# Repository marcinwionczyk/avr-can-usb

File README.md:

##avr-can-usb firmware

This code is under development and is not mature.

I'm using chips like: atmega644pa, MCP2515, TJA1042T.
Communication with PC is done over UART-USB converter FT230XS and is galvanically separated from the rest chips with 
VO0611 optocouplers.

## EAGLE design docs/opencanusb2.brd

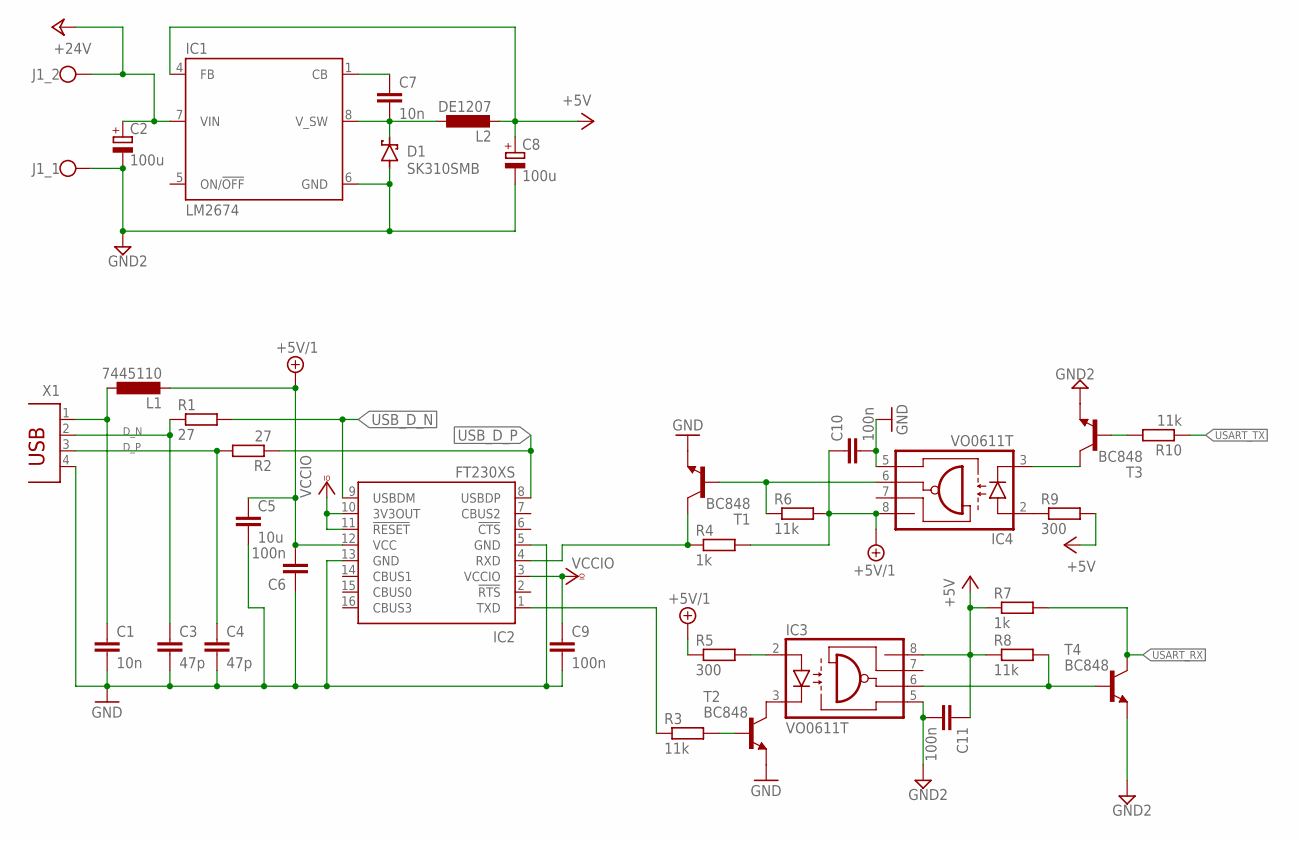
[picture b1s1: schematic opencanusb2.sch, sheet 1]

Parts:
C1: 10n; C0402
C2, C8: 100u; E5-8,5
C3, C4: 47p; C0603
C5: 10u; C1210K
C6, C9, C10, C11: 100n; C0805
C7: 10n; C0805
D1: SK310SMB; SMB
IC1: LM2674; SOIC127P599X265-8N
IC2: FT230XS; SSOP16
IC3, IC4: VO0611T; SOIC127P610X323-8N
J1: DG300-7.5
L1: 7445110
L2: DE1207; INDC120120X800N
R1, R2: 27; R0805
R3, R6, R8, R10: 11k; R1206
R4, R7: 1k; R0805
R5, R9: 300; R0805
T1, T2, T3, T4: BC848; SOT23
X1: PN61729

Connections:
+5V: C8.+, C11.1, IC1.4 (FB), IC3.8 (VCC), L2.2, R7.1, R8.1, R9.2; also elsewhere on the board
+5V/1: C5.1, C6.2, C10.1, IC2.12 (VCC), IC4.8 (VCC), L1.2, R4.2, R5.1, R6.2
+24V: C2.+, IC1.7 (VIN), J1.P$2; also elsewhere on the board
D_N: C3.1, R1.1, X1.2
D_P: C4.1, R2.2, X1.3
GND: C1.2, C3.2, C4.2, C5.2, C6.1, C9.2, C10.2, IC2.5 (GND), IC2.13 (GND), IC4.5 (GND), T1.2 (E), T2.2 (E), X1.4
GND2: C2.-, C8.-, C11.2, D1.A, IC1.6 (GND), IC3.5 (GND), J1.P$1, T3.2 (E), T4.2 (E); also elsewhere on the board
unnamed: IC3.2 (A), R5.2
unnamed: IC2.1 (TXD), R3.1
unnamed: IC3.3 (C), T2.3 (C)
unnamed: IC4.2 (A), R9.1
unnamed: IC4.3 (C), T3.3 (C)
unnamed: IC4.6 (VO), R6.1, T1.1 (B)
unnamed: R3.2, T2.1 (B)
unnamed: IC3.6 (VO), R8.2, T4.1 (B)
unnamed: R10.2, T3.1 (B)
unnamed: IC2.4 (RXD), R4.1, T1.3 (C)
unnamed: C1.1, L1.1, X1.1
unnamed: C7.2, D1.C, IC1.8 (V_SW), L2.1
unnamed: C7.1, IC1.1 (CB)
ON/!OFF: IC1.5 (ON/!OFF)
USART_RX: R7.2, T4.3 (C); also elsewhere on the board
USART_TX: R10.1; also elsewhere on the board
USB_D_N: IC2.9 (USBDM), R1.2
USB_D_P: IC2.8 (USBDP), R2.1
VCCIO: C9.1, IC2.3 (VCCIO), IC2.10 (3V3OUT), IC2.11 (!RESET)

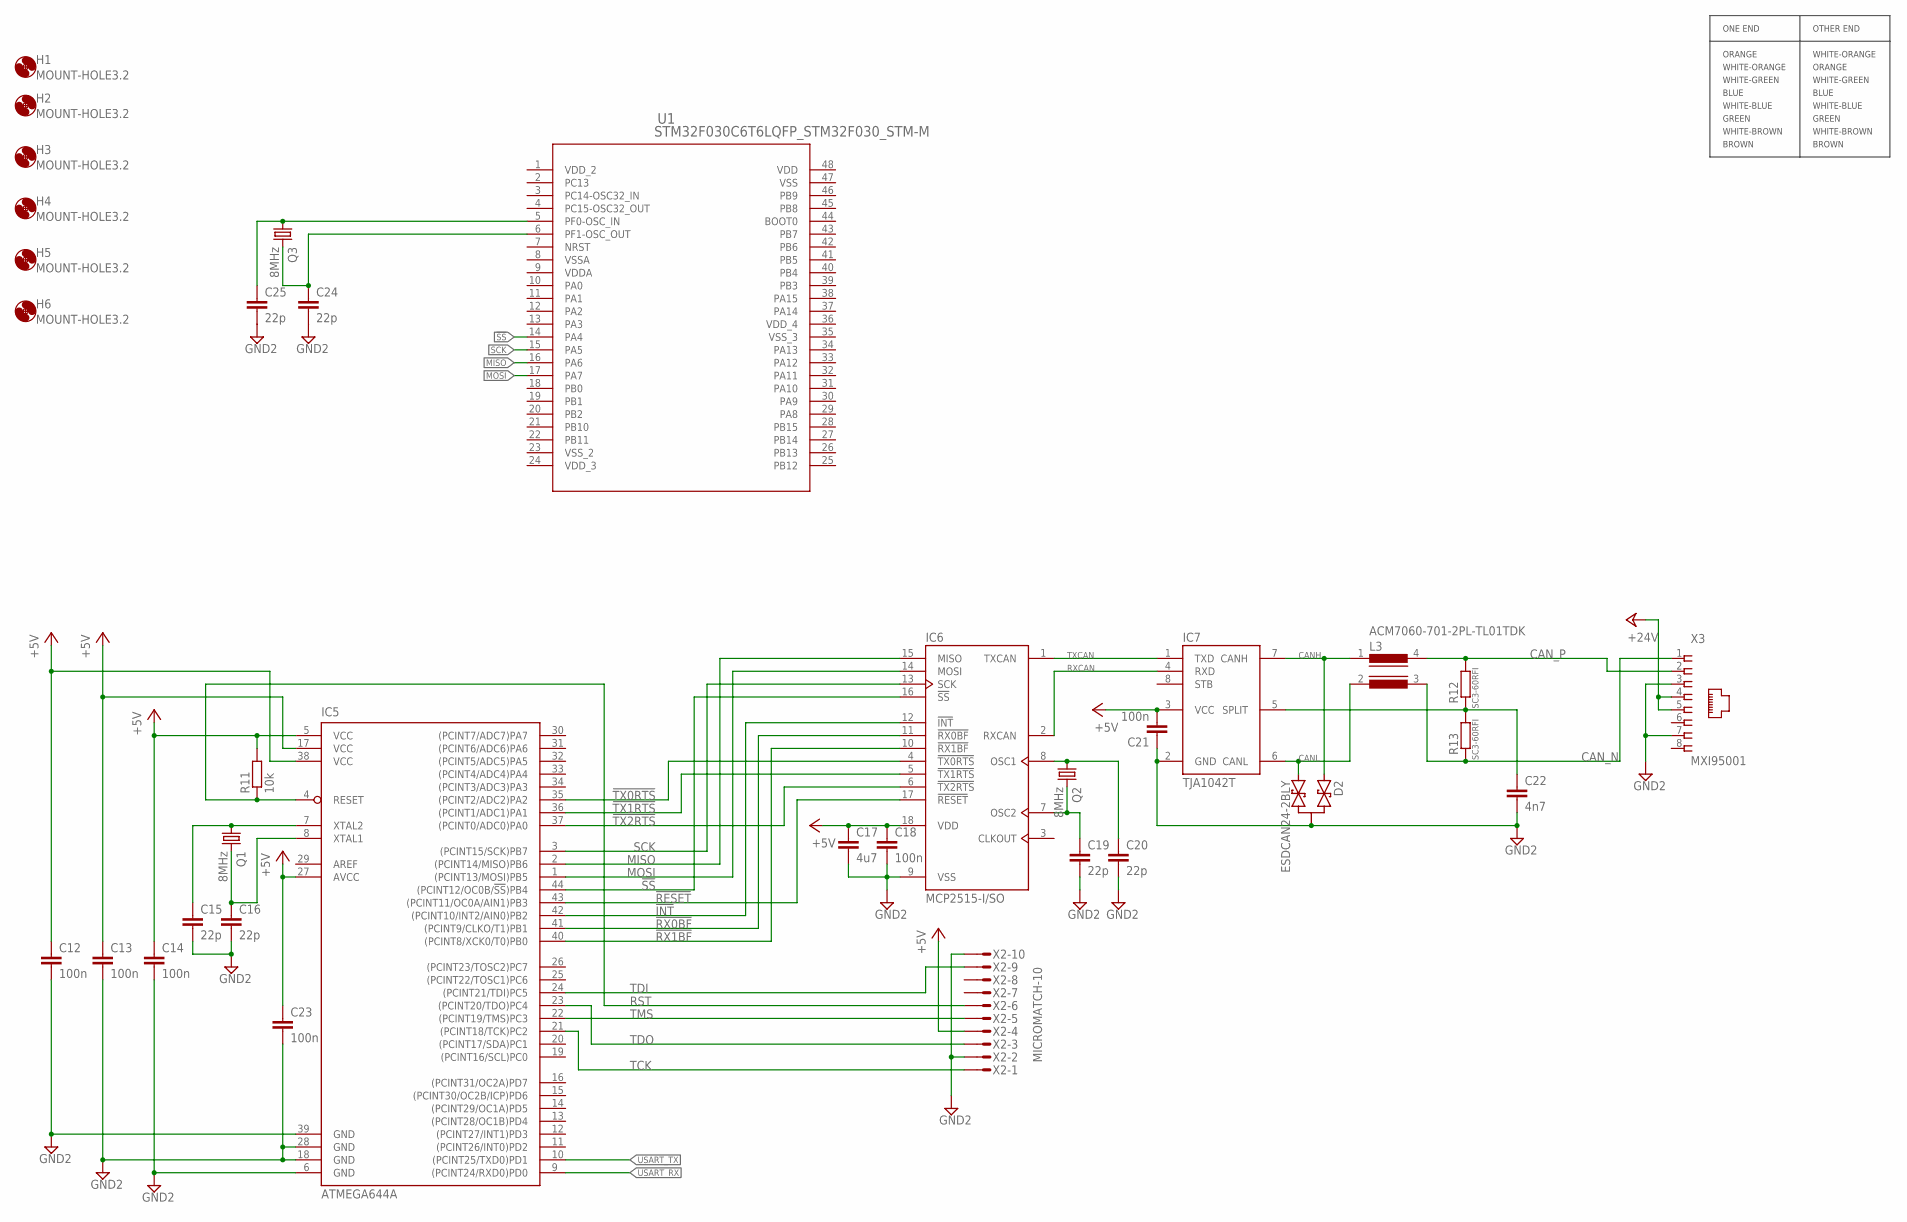
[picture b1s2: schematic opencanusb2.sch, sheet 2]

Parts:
C12, C13, C14, C18, C21, C23: 100n; C0805
C15, C16, C19, C20, C24, C25: 22p; C0805
C17: 4u7; C0805
C22: 4n7; C0805
D2: ESDCAN24-2BLY; SOT95P255X140-3N
H1, H2, H3, H4, H5, H6: MOUNT-HOLE3.2; 3,2
IC5: ATMEGA644A; TQFP44
IC6: MCP2515-I/SO; SOIC127P1030X265-18N
IC7: TJA1042T; SOIC127P600X265-8N
L3: ACM7060-701-2PL-TL01TDK
Q1, Q2, Q3: 8MHz; HC49UP
R11: 10k; R1206
R12, R13: SC3-60RFI; RESC3163X76N
U1: STM32F030C6T6LQFP_STM32F030_STM-M; LQFP_STM32F030_STM-M
X2: MICROMATCH-10
X3: MXI95001; MXI950001

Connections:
!INT: IC5.42 ((PCINT10/INT2/AIN0)PB2), IC6.12 (!INT)
!RESET: IC5.43 ((PCINT11/OC0A/AIN1)PB3), IC6.17 (!RESET)
!RX0BF: IC5.41 ((PCINT9/CLKO/T1)PB1), IC6.11 (!RX0BF)
!RX1BF: IC5.40 ((PCINT8/XCK0/T0)PB0), IC6.10 (!RX1BF)
!SS: IC5.44 ((PCINT12/OC0B/!SS!)PB4), IC6.16 (!SS), U1.14 (PA4)
!TX0RTS: IC5.35 ((PCINT2/ADC2)PA2), IC6.4 (!TX0RTS)
!TX1RTS: IC5.36 ((PCINT1/ADC1)PA1), IC6.5 (!TX1RTS)
!TX2RTS: IC5.37 ((PCINT0/ADC0)PA0), IC6.6 (!TX2RTS)
+5V: C12.1, C13.1, C14.1, C17.1, C18.1, C21.2, C23.1, IC5.5 (VCC), IC5.17 (VCC), IC5.27 (AVCC), IC5.38 (VCC), IC6.18 (VDD), IC7.3 (VCC), R11.2, X2.4; also elsewhere on the board
+24V: X3.4, X3.5; also elsewhere on the board
CANH: D2.1, IC7.7 (CANH), L3.1
CANL: D2.2, IC7.6 (CANL), L3.2
CAN_N: L3.3, R13.1, X3.1
CAN_P: L3.4, R12.2, X3.2
GND2: C12.2, C13.2, C14.2, C15.2, C16.2, C17.2, C18.2, C19.2, C20.2, C21.1, C22.2, C23.2, C24.2, C25.2, D2.3, IC5.6 (GND), IC5.18 (GND), IC5.28 (GND), IC5.39 (GND), IC6.9 (VSS), IC7.2 (GND), X2.2, X2.10, X3.3, X3.7; also elsewhere on the board
MISO: IC5.2 ((PCINT14/MISO)PB6), IC6.15 (MISO), U1.16 (PA6)
MOSI: IC5.1 ((PCINT13/MOSI)PB5), IC6.14 (MOSI), U1.17 (PA7)
unnamed: C25.1, Q3.1, U1.5 (PF0-OSC_IN)
unnamed: C24.1, Q3.2, U1.6 (PF1-OSC_OUT)
unnamed: C15.1, IC5.7 (XTAL2), Q1.1
unnamed: C19.1, IC6.7 (OSC2), Q2.2
unnamed: C16.1, IC5.8 (XTAL1), Q1.2
unnamed: C20.1, IC6.8 (OSC1), Q2.1
unnamed: C22.1, IC7.5 (SPLIT), R12.1, R13.2
RST: IC5.4 (RESET), R11.1, X2.6
RXCAN: IC6.2 (RXCAN), IC7.4 (RXD)
SCK: IC5.3 ((PCINT15/SCK)PB7), IC6.13 (SCK), U1.15 (PA5)
TCK: IC5.21 ((PCINT18/TCK)PC2), X2.1
TDI: IC5.24 ((PCINT21/TDI)PC5), X2.9
TDO: IC5.23 ((PCINT20/TDO)PC4), X2.3
TMS: IC5.22 ((PCINT19/TMS)PC3), X2.5
TXCAN: IC6.1 (TXCAN), IC7.1 (TXD)
USART_RX: IC5.9 ((PCINT24/RXD0)PD0); also elsewhere on the board
USART_TX: IC5.10 ((PCINT25/TXD0)PD1); also elsewhere on the board
VDD: U1.48 (VDD)
VDDA: U1.9 (VDDA)
VDD_2: U1.1 (VDD_2)
VDD_3: U1.24 (VDD_3)
VDD_4: U1.36 (VDD_4)

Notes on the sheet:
ORANGE
WHITE-ORANGE
WHITE-GREEN
BLUE
WHITE-BLUE
GREEN
WHITE-BROWN
ONE END
OTHER END
BROWN

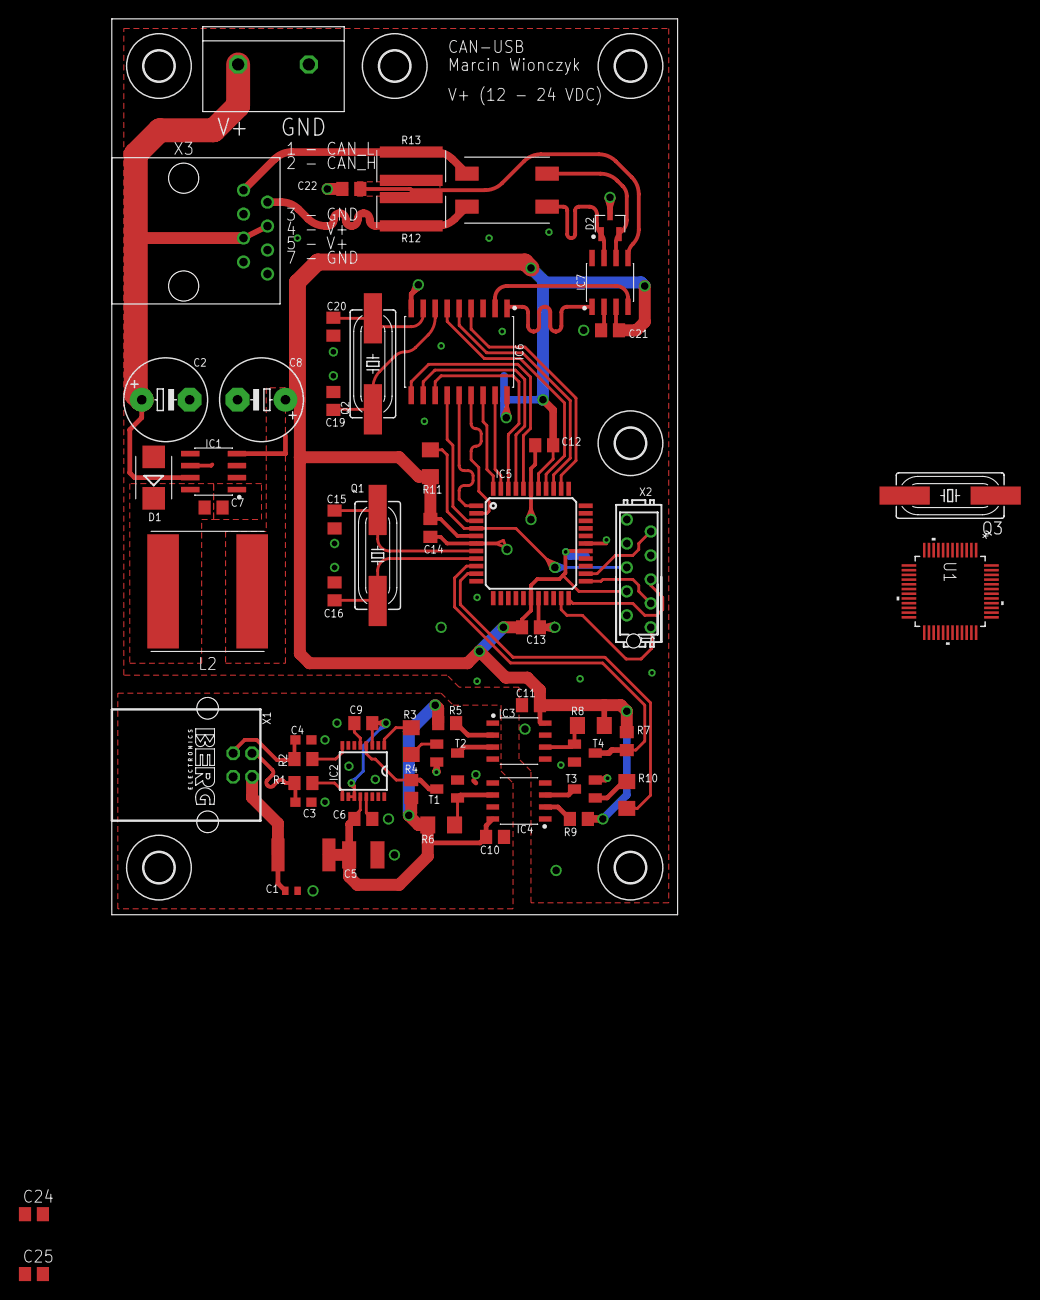
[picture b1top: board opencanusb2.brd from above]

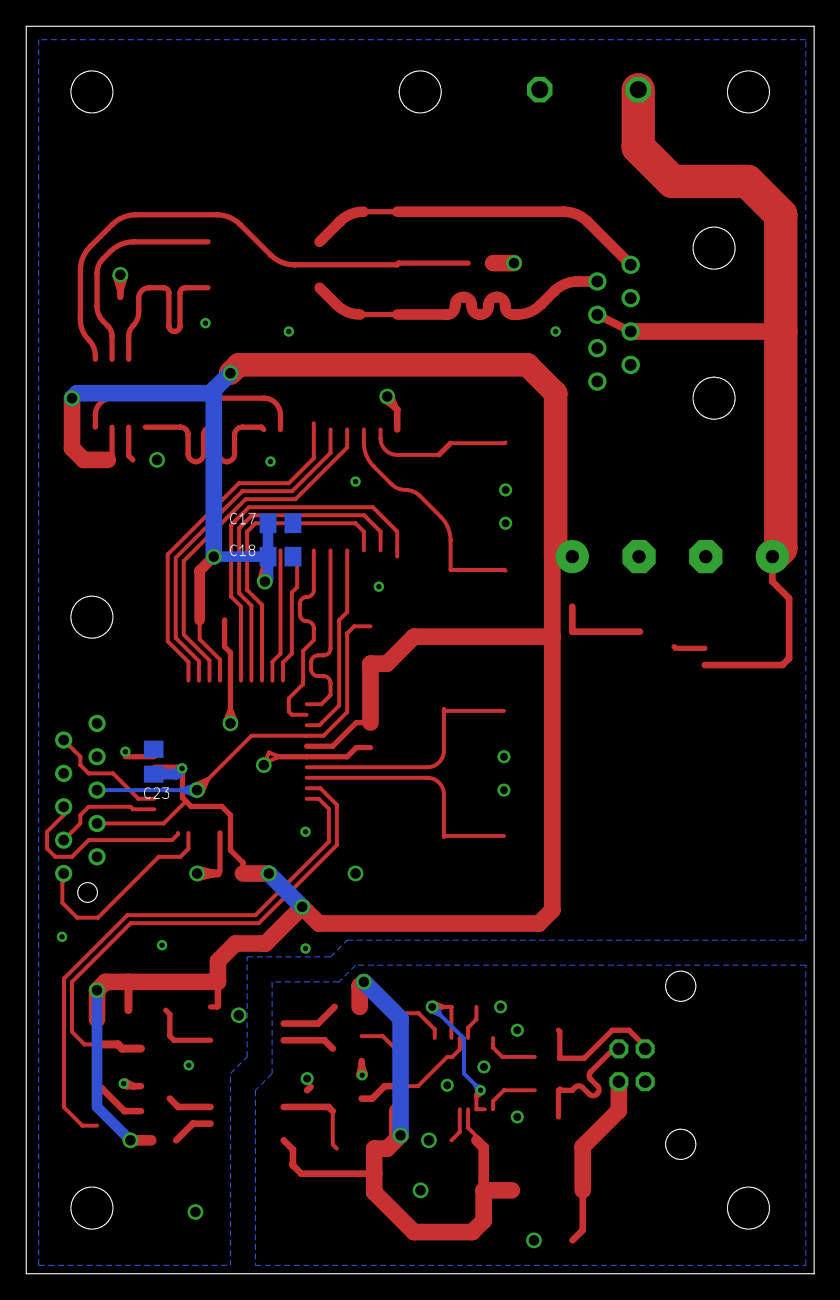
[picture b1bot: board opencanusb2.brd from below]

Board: 2 copper layers, 60.0 x 95.0 mm, 68 parts (3 on the bottom side), 54 nets.

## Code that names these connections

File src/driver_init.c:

/**
 * \file
 *
 * \brief Driver initialization.
 *
 (c) 2020 Microchip Technology Inc. and its subsidiaries.

    Subject to your compliance with these terms,you may use this software and
    any derivatives exclusively with Microchip products.It is your responsibility
    to comply with third party license terms applicable to your use of third party
    software (including open source software) that may accompany Microchip software.

    THIS SOFTWARE IS SUPPLIED BY MICROCHIP "AS IS". NO WARRANTIES, WHETHER
    EXPRESS, IMPLIED OR STATUTORY, APPLY TO THIS SOFTWARE, INCLUDING ANY IMPLIED
    WARRANTIES OF NON-INFRINGEMENT, MERCHANTABILITY, AND FITNESS FOR A
    PARTICULAR PURPOSE.

    IN NO EVENT WILL MICROCHIP BE LIABLE FOR ANY INDIRECT, SPECIAL, PUNITIVE,
    INCIDENTAL OR CONSEQUENTIAL LOSS, DAMAGE, COST OR EXPENSE OF ANY KIND
    WHATSOEVER RELATED TO THE SOFTWARE, HOWEVER CAUSED, EVEN IF MICROCHIP HAS
    BEEN ADVISED OF THE POSSIBILITY OR THE DAMAGES ARE FORESEEABLE. TO THE
    FULLEST EXTENT ALLOWED BY LAW, MICROCHIP'S TOTAL LIABILITY ON ALL CLAIMS IN
    ANY WAY RELATED TO THIS SOFTWARE WILL NOT EXCEED THE AMOUNT OF FEES, IF ANY,
    THAT YOU HAVE PAID DIRECTLY TO MICROCHIP FOR THIS SOFTWARE.
 *
 */

/*
 * Code generated by START.
 *
 * This file will be overwritten when reconfiguring your START project.
 * Please copy examples or other code you want to keep to a separate file
 * to avoid losing it when reconfiguring.
 */

#include "driver_init.h"
#include <system.h>

void EXTERNAL_IRQ_0_initialization(void)
{

	// Set pin direction to input
	RX1BF_set_dir(PORT_DIR_IN);

	RX1BF_set_pull_mode(
	    // <y> Pull configuration
	    // <id> pad_pull_config
	    // <PORT_PULL_OFF"> Off
	    // <PORT_PULL_UP"> Pull-up
	    PORT_PULL_OFF);

	// Set pin direction to input
	RX0BF_set_dir(PORT_DIR_IN);

	RX0BF_set_pull_mode(
	    // <y> Pull configuration
	    // <id> pad_pull_config
	    // <PORT_PULL_OFF"> Off
	    // <PORT_PULL_UP"> Pull-up
	    PORT_PULL_OFF);

	// Set pin direction to input
	INT_set_dir(PORT_DIR_IN);

	INT_set_pull_mode(
	    // <y> Pull configuration
	    // <id> pad_pull_config
	    // <PORT_PULL_OFF"> Off
	    // <PORT_PULL_UP"> Pull-up
	    PORT_PULL_OFF);

	EXTERNAL_IRQ_0_init();
}

/* configure the pins and initialize the registers */
void SPI_0_initialization(void)
{

	// Set pin direction to input
	MISO_set_dir(PORT_DIR_IN);

	MISO_set_pull_mode(
	    // <y> Pull configuration
	    // <id> pad_pull_config
	    // <PORT_PULL_OFF"> Off
	    // <PORT_PULL_UP"> Pull-up
	    PORT_PULL_OFF);

	// Set pin direction to output
	MOSI_set_dir(PORT_DIR_OUT);

	MOSI_set_level(
	    // <y> Initial level
	    // <id> pad_initial_level
	    // <false"> Low
	    // <true"> High
	    false);

	// Set pin direction to output
	SCK_set_dir(PORT_DIR_OUT);

	SCK_set_level(
	    // <y> Initial level
	    // <id> pad_initial_level
	    // <false"> Low
	    // <true"> High
	    false);

	SPI_0_init();
}

void TIMER_0_initialization(void)
{

    TIMER_0_init();
}

/* configure pins and initialize registers */
void USART_0_initialization(void)
{

	// Set pin direction to input
	USART_RX_set_dir(PORT_DIR_IN);

	USART_RX_set_pull_mode(
	    // <y> Pull configuration
	    // <id> pad_pull_config
	    // <PORT_PULL_OFF"> Off
	    // <PORT_PULL_UP"> Pull-up
	    PORT_PULL_OFF);

	// Set pin direction to output
	USART_TX_set_dir(PORT_DIR_OUT);

	USART_TX_set_level(
	    // <y> Initial level
	    // <id> pad_initial_level
	    // <false"> Low
	    // <true"> High
	    false);

	USART_0_init();
}

/**
 * \brief System initialization
 */
void system_init()
{
	mcu_init();

	/* PORT setting on PA0 */

	// Set pin direction to output
	TX2RTS_set_dir(PORT_DIR_OUT);

	TX2RTS_set_level(
	    // <y> Initial level
	    // <id> pad_initial_level
	    // <false"> Low
	    // <true"> High
	    true);

	/* PORT setting on PA1 */

	// Set pin direction to output
	TX1RTS_set_dir(PORT_DIR_OUT);

	TX1RTS_set_level(
	    // <y> Initial level
	    // <id> pad_initial_level
	    // <false"> Low
	    // <true"> High
	    true);

	/* PORT setting on PA2 */

	// Set pin direction to output
	TX0RTS_set_dir(PORT_DIR_OUT);

	TX0RTS_set_level(
	    // <y> Initial level
	    // <id> pad_initial_level
	    // <false"> Low
	    // <true"> High
	    true);

	/* PORT setting on PB3 */

	// Set pin direction to output
	RESET_set_dir(PORT_DIR_OUT);

	RESET_set_level(
	    // <y> Initial level
	    // <id> pad_initial_level
	    // <false"> Low
	    // <true"> High
	    true);

	/* PORT setting on PB4 */

	// Set pin direction to output
	SS_set_dir(PORT_DIR_OUT);

	SS_set_level(
	    // <y> Initial level
	    // <id> pad_initial_level
	    // <false"> Low
	    // <true"> High
	    true);

	sysctrl_init();

	FLASH_0_init();

	EXTERNAL_IRQ_0_initialization();

	SPI_0_initialization();
    TIMER_0_initialization();
	USART_0_initialization();
}

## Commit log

2021-07-17 This shit compiles and I'm good to go
2021-07-17 added traget "check_size" to CMakeLists.txt added #include <avr/common.h> to protected_io.S in case of missing SREG
2021-07-30 added files generated by atmel start

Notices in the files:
parts and their libraries:
COPYRIGHT: Copyright (C) 2018 Accelerated Designs. All rights reserved
